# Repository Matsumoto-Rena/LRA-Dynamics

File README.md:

# LRA-Dynamics
-1201_LRA_web_v3
  - ArduinoIDEで開いて下さい 
  - WifiのSSIDとパスワードをパソコンの接続先と合わせます．
  - プログラムを実行するとシリアルモニタに数字が返ってくるのでブラウザにコピペしてください
  - rep12 res3で赤青方向 rep15 res1で緑黃方向に動きます

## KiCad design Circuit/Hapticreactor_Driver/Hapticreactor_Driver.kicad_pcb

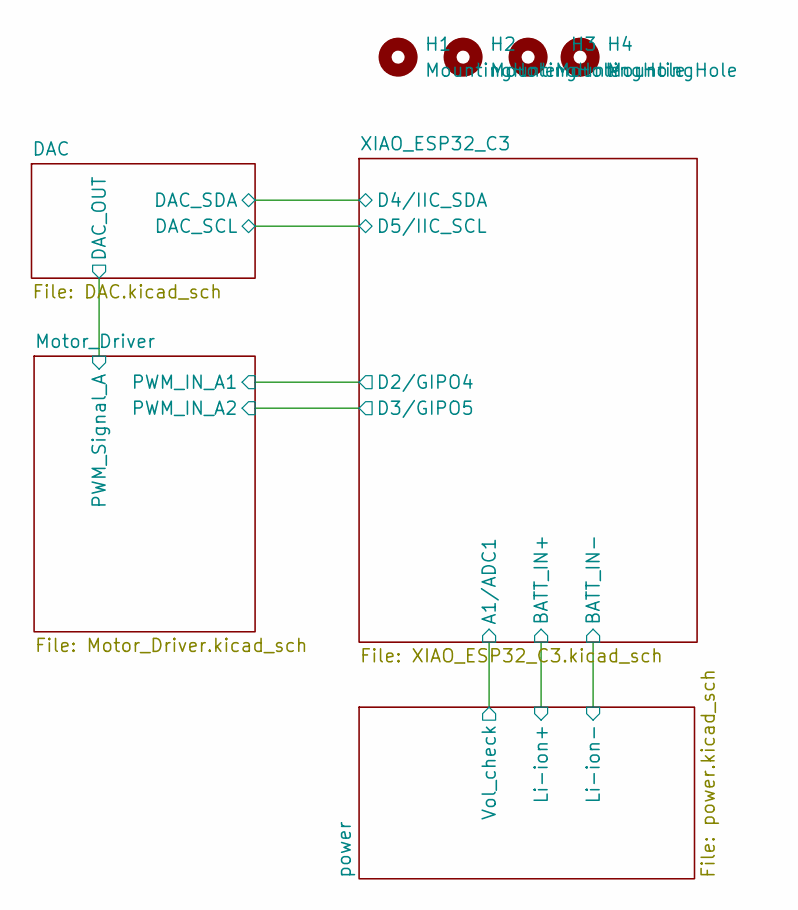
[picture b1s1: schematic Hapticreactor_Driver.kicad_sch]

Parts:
H1, H2, H3, H4: MountingHole; MountingHole_2.2mm_M2

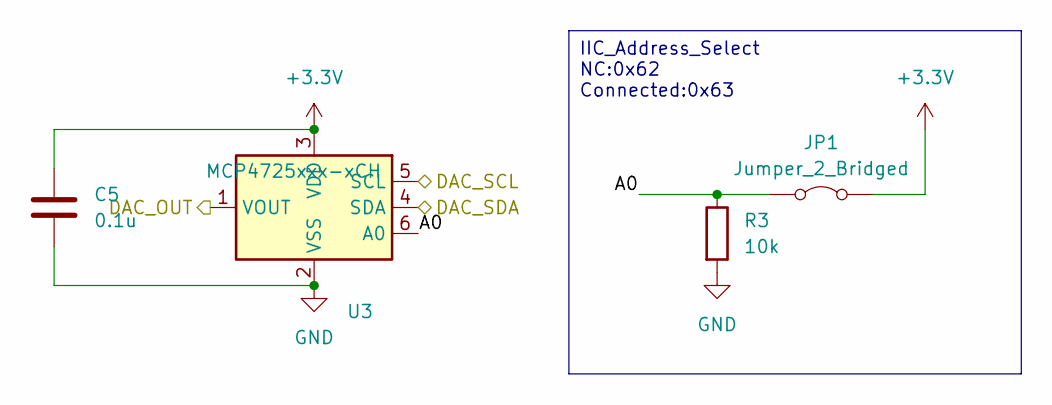
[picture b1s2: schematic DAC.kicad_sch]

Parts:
C5: 0.1u; C_0603_1608Metric_Pad1.08x0.95mm_HandSolder
JP1: Jumper_2_Bridged; SolderJumper-2_P1.3mm_Open_TrianglePad1.0x1.5mm
R3: 10k; R_0603_1608Metric_Pad0.98x0.95mm_HandSolder
U3: MCP4725xxx-xCH; SOT-23-6

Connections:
+3.3V: C5.1, JP1.2 (B), U3.3 (VDD); also elsewhere on the board
/DAC/A0: JP1.1 (A), R3.1, U3.6 (A0)
/DAC/DAC_OUT: U3.1 (VOUT); also elsewhere on the board
/DAC/DAC_SCL: U3.5 (SCL); also elsewhere on the board
/DAC/DAC_SDA: U3.4 (SDA); also elsewhere on the board
GND: C5.2, R3.2, U3.2 (VSS); also elsewhere on the board

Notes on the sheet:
IIC_Address_Select NC:0x62 Connected:0x63

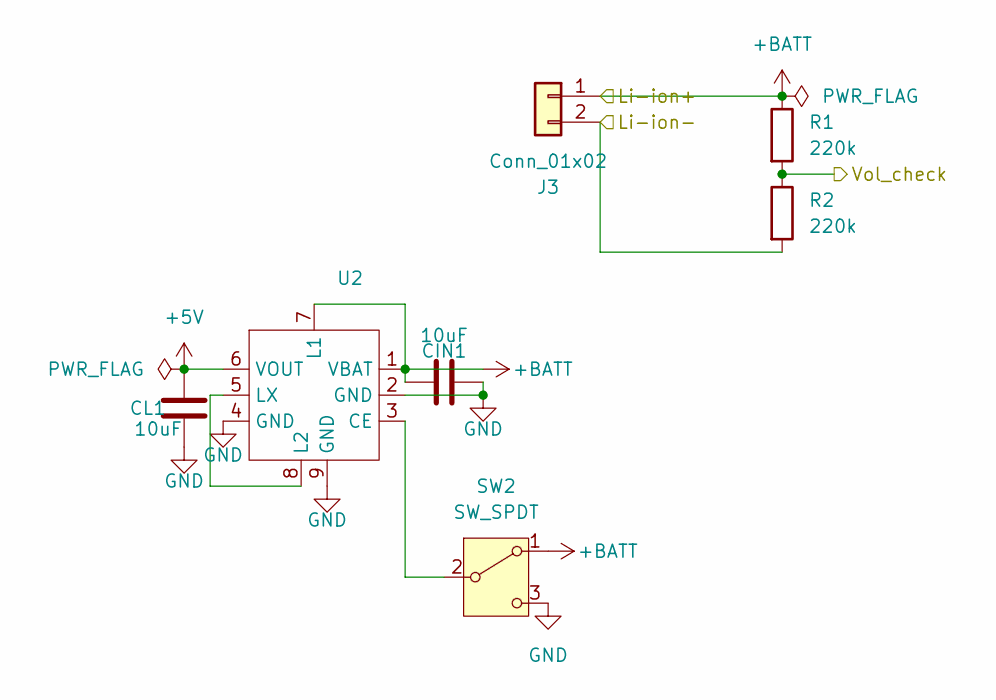
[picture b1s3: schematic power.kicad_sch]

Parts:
CIN1: 10uF; C_0603_1608Metric
CL1: 10uF; C_0603_1608Metric
J3: Conn_01x02; JST_PH_S2B-PH-K_1x02_P2.00mm_Horizontal
R1, R2: 220k; R_0603_1608Metric_Pad0.98x0.95mm_HandSolder
SW2: SW_SPDT; SSAJ120100
U2: XCL102D503CR-G

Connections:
+5V: CL1.2, U2.6 (VOUT); also elsewhere on the board
+BATT: CIN1.1, J3.1, R1.1, SW2.1 (A), U2.1 (VBAT), U2.7 (L1); also elsewhere on the board
/XIAO_ESP32_C3/A1/ADC1: R1.2, R2.1; also elsewhere on the board
/XIAO_ESP32_C3/BATT_IN-: J3.2, R2.2; also elsewhere on the board
GND: CIN1.2, CL1.1, SW2.3 (C), U2.2 (GND), U2.4 (GND), U2.9 (GND); also elsewhere on the board
unnamed: SW2.2 (B), U2.3 (CE)
unnamed: U2.5 (LX), U2.8 (L2)

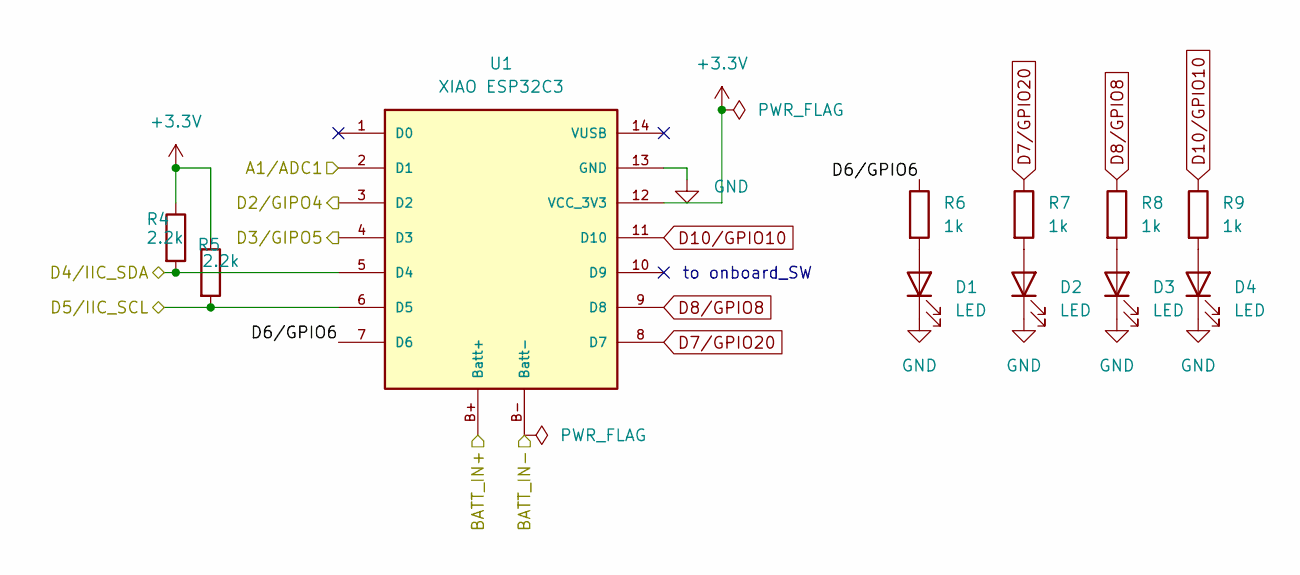
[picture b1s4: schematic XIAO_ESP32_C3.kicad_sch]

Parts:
D1, D2, D3, D4: LED; LED_0603_1608Metric
R4, R5: 2.2k; R_0603_1608Metric_Pad0.98x0.95mm_HandSolder
R6, R7, R8, R9: 1k; R_0603_1608Metric_Pad0.98x0.95mm_HandSolder
U1: XIAO ESP32C3; xiao_esp32c3

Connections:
+3.3V: R4.1, R5.1, U1.12 (VCC_3V3); also elsewhere on the board
+BATT: U1.B+ (Batt+); also elsewhere on the board
/DAC/DAC_SCL: R5.2, U1.6 (D5); also elsewhere on the board
/DAC/DAC_SDA: R4.2, U1.5 (D4); also elsewhere on the board
/Motor_Driver/PWM_IN_A1: U1.3 (D2); also elsewhere on the board
/Motor_Driver/PWM_IN_A2: U1.4 (D3); also elsewhere on the board
/XIAO_ESP32_C3/A1/ADC1: U1.2 (D1); also elsewhere on the board
/XIAO_ESP32_C3/BATT_IN-: U1.B- (Batt-); also elsewhere on the board
/XIAO_ESP32_C3/D6/GPIO6: R6.1, U1.7 (D6)
D7/GPIO20: R7.1, U1.8 (D7)
D8/GPIO8: R8.1, U1.9 (D8)
D10/GPIO10: R9.1, U1.11 (D10)
GND: D1.1 (K), D2.1 (K), D3.1 (K), D4.1 (K), U1.13 (GND); also elsewhere on the board
unnamed: D1.2 (A), R6.2
unnamed: D2.2 (A), R7.2
unnamed: D3.2 (A), R8.2
unnamed: D4.2 (A), R9.2

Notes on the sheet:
to onboard_SW

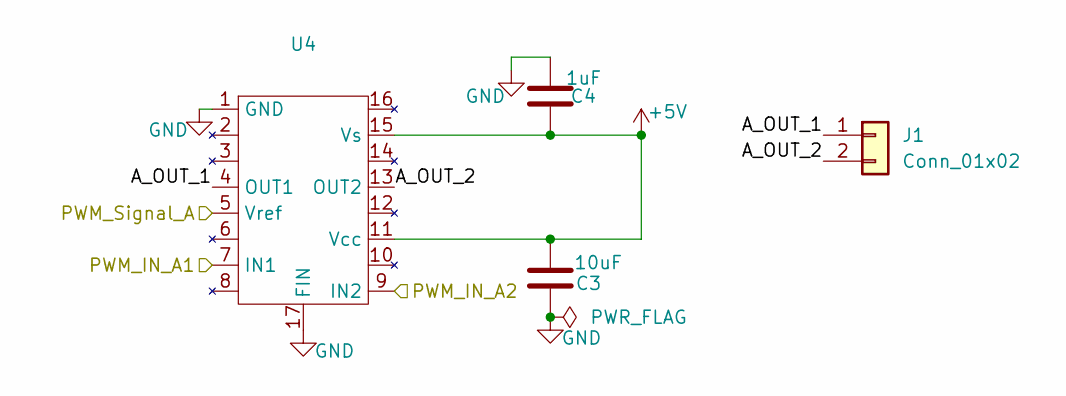
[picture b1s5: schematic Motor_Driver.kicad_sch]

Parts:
C3: 10uF; C_0603_1608Metric
C4: 1uF; C_0603_1608Metric
J1: Conn_01x02; PinHeader_1x02_P2.00mm_Vertical
U4: TA7291F

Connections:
+5V: C3.2, C4.1, U4.11 (Vcc), U4.15 (Vs); also elsewhere on the board
/DAC/DAC_OUT: U4.5 (Vref); also elsewhere on the board
/Motor_Driver/A_OUT_1: J1.1, U4.4 (OUT1)
/Motor_Driver/A_OUT_2: J1.2, U4.13 (OUT2)
/Motor_Driver/PWM_IN_A1: U4.7 (IN1); also elsewhere on the board
/Motor_Driver/PWM_IN_A2: U4.9 (IN2); also elsewhere on the board
GND: C3.1, C4.2, U4.1 (GND), U4.17 (FIN); also elsewhere on the board

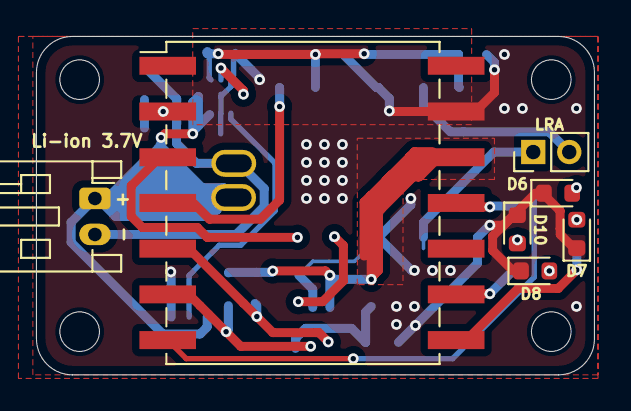
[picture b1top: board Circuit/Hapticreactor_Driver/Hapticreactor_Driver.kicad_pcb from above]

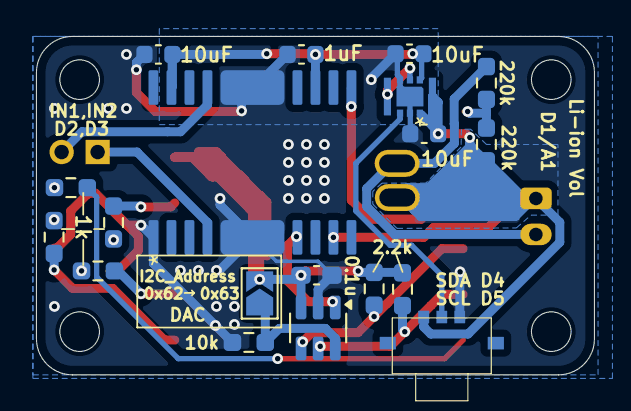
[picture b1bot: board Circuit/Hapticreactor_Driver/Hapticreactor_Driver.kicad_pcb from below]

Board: 2 copper layers, 31.0 x 18.8 mm, 30 parts (19 on the bottom side), 24 nets.

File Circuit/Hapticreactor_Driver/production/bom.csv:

Designator,Footprint,Quantity,Value,LCSC Part #
"C3, CIN1, CL1",0603,3,10uF,
C4,0603,1,1uF,
C5,0603,1,0.1u,
"D1, D2, D3, D4",0603,4,LED,
J1,PinHeader_1x02_P2.00mm_Vertical,1,Conn_01x02,
J3,JST_PH_S2B-PH-K_1x02_P2.00mm_Horizontal,1,Conn_01x02,
JP1,SolderJumper-2_P1.3mm_Open_TrianglePad1.0x1.5mm,1,Jumper_2_Bridged,
"R1, R2",0603,2,220k,
R3,0603,1,10k,
"R4, R5",0603,2,2.2k,
"R6, R7, R8, R9",0603,4,1k,
SW2,SSAJ120100,1,SW_SPDT,
U1,xiao_esp32c3,1,XIAO ESP32C3,
U2,XCL102D503CR-G,1,~,
U3,SOT-23-6,1,MCP4725xxx-xCH,
U4,TA7291F,1,~,

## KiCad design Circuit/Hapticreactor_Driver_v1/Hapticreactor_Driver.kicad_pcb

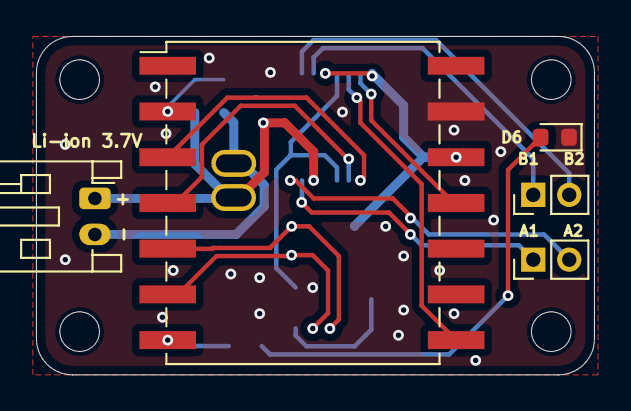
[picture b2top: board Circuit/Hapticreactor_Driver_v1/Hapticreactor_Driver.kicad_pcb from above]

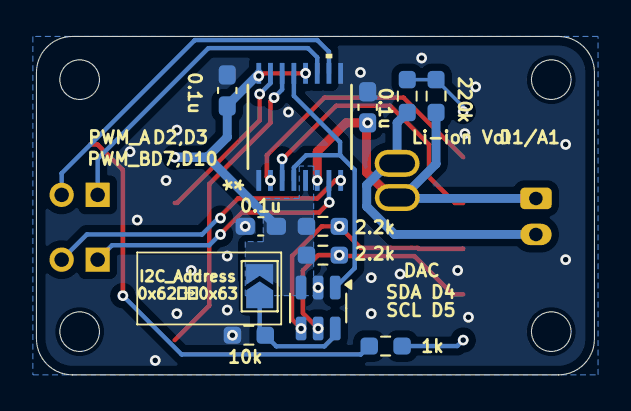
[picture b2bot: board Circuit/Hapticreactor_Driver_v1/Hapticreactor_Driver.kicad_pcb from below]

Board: 2 copper layers, 31.0 x 18.8 mm, 21 parts (12 on the bottom side), 19 nets.

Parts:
C1, C2, C5: 0.1u; C_0603_1608Metric_Pad1.08x0.95mm_HandSolder
D1: LED; LED_0603_1608Metric
H1, H2, H3, H4: MountingHole; MountingHole_2.2mm_M2
J1, J2: Conn_01x02; PinHeader_1x02_P2.00mm_Vertical
J3: Conn_01x02; JST_PH_S2B-PH-K_1x02_P2.00mm_Horizontal
JP1: Jumper_2_Bridged; SolderJumper-2_P1.3mm_Open_TrianglePad1.0x1.5mm
R1, R2: 220k; R_0603_1608Metric_Pad0.98x0.95mm_HandSolder
R3: 10k; R_0603_1608Metric_Pad0.98x0.95mm_HandSolder
R4, R5: 2.2k; R_0603_1608Metric_Pad0.98x0.95mm_HandSolder
R6: 1k; R_0603_1608Metric_Pad0.98x0.95mm_HandSolder
U1: XIAO ESP32C3; xiao_esp32c3
U2: TB6552FNG_C_8_EL; TB6552FNG
U3: MCP4725xxx-xCH; SOT-23-6

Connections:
+3.3V: C1.1, C5.1, JP1.2 (B), R4.1, R5.1, U1.12 (VCC_3V3), U2.5 (ASTBY), U2.12 (BSTBY), U2.16 (VCC), U3.3 (VDD)
+BATT: C2.1, J3.1, R1.1, U1.B+ (Batt+), U2.6 (VM)
/DAC/A0: JP1.1 (A), R3.1, U3.6 (A0)
/DAC/DAC_OUT: U2.4 (APWM), U2.13 (BPWM), U3.1 (VOUT)
/DAC/DAC_SCL: R5.2, U1.6 (D5), U3.5 (SCL)
/DAC/DAC_SDA: R4.2, U1.5 (D4), U3.4 (SDA)
/Motor_Driver/A_OUT_1: J1.1, U2.7 (AO1)
/Motor_Driver/A_OUT_2: J1.2, U2.8 (AO2)
/Motor_Driver/B_OUT_1: J2.1, U2.11 (BO1)
/Motor_Driver/B_OUT_2: J2.2, U2.10 (BO2)
/Motor_Driver/PWM_IN_A1: U1.3 (D2), U2.2 (AIN1)
/Motor_Driver/PWM_IN_A2: U1.4 (D3), U2.3 (AIN2)
/Motor_Driver/PWM_IN_B1: U1.11 (D10), U2.15 (BIN1)
/Motor_Driver/PWM_IN_B2: U1.8 (D7), U2.14 (BIN2)
/XIAO_ESP32_C3/A1/ADC1: R1.2, R2.1, U1.2 (D1)
/XIAO_ESP32_C3/BATT_IN-: J3.2, R2.2, U1.B- (Batt-)
/XIAO_ESP32_C3/D6/GPIO6: R6.1, U1.7 (D6)
GND: C1.2, C2.2, C5.2, D1.1 (K), R3.2, U1.13 (GND), U2.1 (GND), U2.9 (PGND), U3.2 (VSS)
unnamed: D1.2 (A), R6.2

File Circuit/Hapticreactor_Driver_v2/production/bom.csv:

Designator,Footprint,Quantity,Value,LCSC Part #
"C1, C2, C5",0603,3,0.1u,
D1,0603,1,LED,
"J1, J2",PinHeader_1x02_P2.00mm_Vertical,2,Conn_01x02,
J3,JST_PH_S2B-PH-K_1x02_P2.00mm_Horizontal,1,Conn_01x02,
JP1,SolderJumper-2_P1.3mm_Open_TrianglePad1.0x1.5mm,1,Jumper_2_Bridged,
"R1, R2",0603,2,220k,
R3,0603,1,10k,
"R4, R5",0603,2,2.2k,
R6,0603,1,1k,
U1,xiao_esp32c3,1,XIAO ESP32C3,
U2,TB6552FNG,1,TB6552FNG_C_8_EL,
U3,SOT-23-6,1,MCP4725xxx-xCH,

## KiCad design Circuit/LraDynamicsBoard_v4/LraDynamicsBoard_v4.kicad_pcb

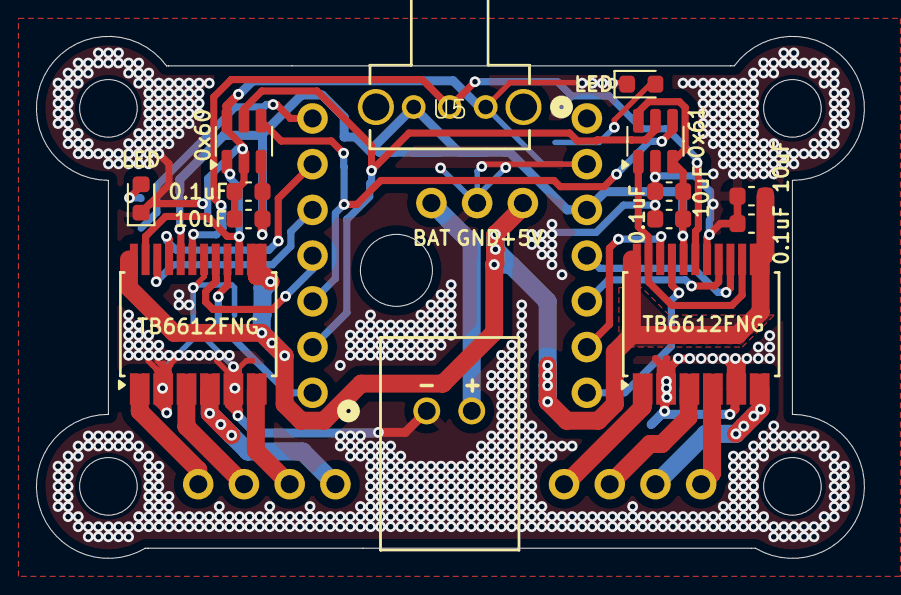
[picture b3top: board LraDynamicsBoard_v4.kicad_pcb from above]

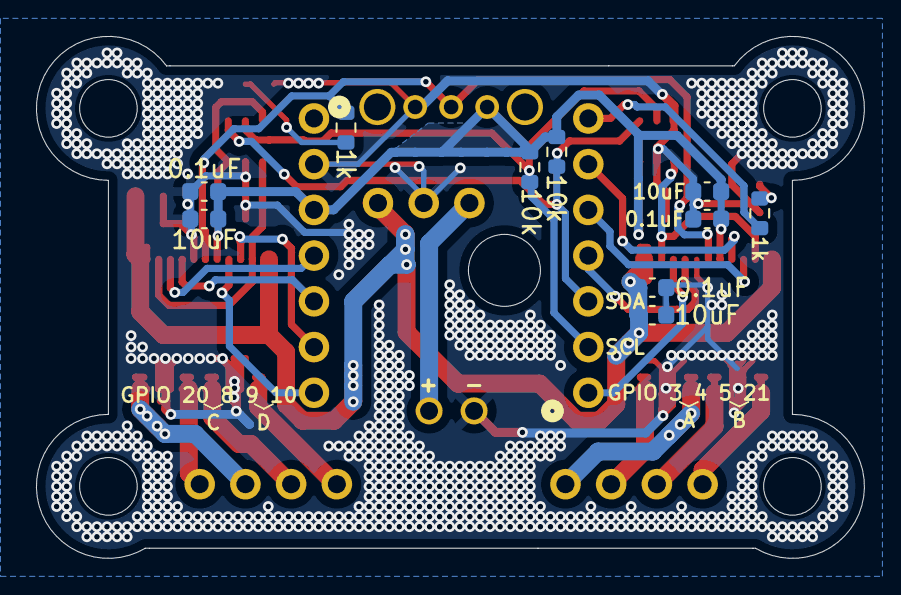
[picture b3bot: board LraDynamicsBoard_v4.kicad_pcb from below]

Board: 2 copper layers, 46.0 x 29.0 mm, 32 parts (10 on the bottom side), 28 nets.

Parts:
C1, C3, C6, C8, C10, C11: 0.1uF; C_0603_1608Metric
C2, C4, C12, C13, C14, C15: 10uF; C_0603_1608Metric
D1, D2: LED; LED_0603_1608Metric
H1, H2, H3, H4: MountingHole; MountingHole_3.2mm_M3
J1, J2: Conn_01x04; KF128-4P
J3: Conn_01x03; XCL103
J4: Conn_01x02; CONN_S2B-XH-A-1LFSN_JST
R1, R2: 10k; R_0603_1608Metric
R5, R6: 1k; R_0603_1608Metric
SW1: SW_SPDT; OS102011MA1QN1_CNK
U1, U2: MCP4725xxx-xCH; SOT-23-6
U3, U4: TB6612FNG; SSOP-24_5.3x8.2mm_P0.65mm
U5: XiaoEsp32C3

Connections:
+3V3: C1.1, C2.1, C3.1, C4.1, C6.1, C10.1, C13.1, C15.1, R1.1, R2.1, SW1.3 (C), U1.3 (VDD), U2.3 (VDD), U2.6 (A0), U3.20 (VCC), U4.20 (VCC), U5.11 (3V3)
+5V: C8.1, C11.1, C12.1, C14.1, J3.3, U3.13 (VM2), U3.14 (VM3), U3.24 (VM1), U4.13 (VM2), U4.14 (VM3), U4.24 (VM1)
ANALOG_1: U1.1 (VOUT), U3.15 (PWMB), U3.23 (PWMA)
ANALOG_2: U2.1 (VOUT), U4.15 (PWMB), U4.23 (PWMA)
BAT: J3.1, J4.2
D_A1: U3.21 (AIN1), U5.1 (D1)
D_A2: U3.22 (AIN2), U5.2 (D2)
D_B1: U3.17 (BIN1), U5.3 (D3)
D_B2: U3.16 (BIN2), U5.6 (D6)
D_C1: U4.21 (AIN1), U5.7 (D7)
D_C2: U4.22 (AIN2), U5.8 (D8)
D_D1: U4.17 (BIN1), U5.9 (D9)
D_D2: U4.16 (BIN2), U5.10 (D10)
GND: C1.2, C2.2, C3.2, C4.2, C6.2, C8.2, C10.2, C11.2, C12.2, C13.2, C14.2, C15.2, D1.1 (K), D2.1 (K), J3.2, J4.1, SW1.1 (A), U1.2 (VSS), U1.6 (A0), U2.2 (VSS), U3.3 (PGND1), U3.4 (PGND1), U3.9 (PGND2), U3.10 (PGND2), U3.18 (GND), U4.3 (PGND1), U4.4 (PGND1), U4.9 (PGND2), U4.10 (PGND2), U4.18 (GND), U5.12 (GND)
unnamed: D1.2 (A), R5.2
unnamed: D2.2 (A), R6.2
unnamed: R6.1, U5.0 (D0)
OUT_A1: J1.1, U3.1 (AO1), U3.2 (AO1)
OUT_A2: J1.2, U3.5 (AO2), U3.6 (AO2)
OUT_B1: J1.3, U3.11 (BO1), U3.12 (BO1)
OUT_B2: J1.4, U3.7 (BO2), U3.8 (BO2)
OUT_C1: J2.1, U4.1 (AO1), U4.2 (AO1)
OUT_C2: J2.2, U4.5 (AO2), U4.6 (AO2)
OUT_D1: J2.3, U4.11 (BO1), U4.12 (BO1)
OUT_D2: J2.4, U4.7 (BO2), U4.8 (BO2)
SCL: R1.2, U1.5 (SCL), U2.5 (SCL), U5.5 (D5)
SDA: R2.2, U1.4 (SDA), U2.4 (SDA), U5.4 (D4)
STBY: R5.1, SW1.2 (B), U3.19 (STBY), U4.19 (STBY)

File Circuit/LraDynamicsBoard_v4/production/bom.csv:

Designator,Footprint,Quantity,Value,LCSC Part #
"C1, C10, C11, C3, C6, C8",0603,6,0.1uF,
"C12, C13, C14, C15, C2, C4",0603,6,10uF,
D1,0603,1,ACT,
D2,0603,1,IO2,
"J1, J2",KF128-4P,2,Conn_01x04,
J3,XCL103,1,Conn_01x03,
J4,CONN_S2B-XH-A-1LFSN_JST,1,Conn_01x02,
"R1, R2",0603,2,10k,
"R5, R6",0603,2,1k,
SW1,OS102011MA1QN1_CNK,1,SW_SPDT,
"U1, U2",SOT-23-6,2,MCP4725xxx-xCH,
"U3, U4",SSOP-24_5.3x8.2mm_P0.65mm,2,TB6612FNG,
U5,XiaoEsp32C6,1,~,

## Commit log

2025-08-30 add sample programs
2025-09-01 1秒毎に電流を流す方向が変化する.非対称振動による移動ができてそうな感じがする
2025-09-07 非対称なSin波らしきものを出すことに成功
2025-09-07 アナログ波形をMDに入力しようと試みた
2025-09-12 実験装置のCAD,Arduinoコードをアップロード
2025-09-20 M5StackBasicのDACを使って非対称振動,対象振動を発生させることに成功
2025-09-21 試行錯誤の末,マイクロSDカード内のwavファイルをループ再生することに成功.
2025-09-22 0922ファイルを追加.見事な非対称波形を出してくれます.また,LRAの移動もできているような気がする
2025-09-22 コード先頭に説明文を追加
2025-09-22 手で持つといい感じに二自由度で力を感じる.しかし,床において動かすと,床に接触していない方のLRAの振動がうまく伝わらず思った方向には動かない固定台の構造を変えるべきかもしれない
2025-09-25 LRA2つとM5Stickを一体にし,DS4からの無線コントールすることで,完全独立に動かすことができた,ケーブルうんぬんに悩まなくてすむ.しかし重いのか,移動はしない
2025-09-29 https://robohanactive.slack.com/archives/C08RF0U7A49/p1759132342633789
2025-09-30 まだ途中だけどLRAを無線で動かせてリチウムイオン電池載せれて,MD4チャンネルある基板作ってます.回路図は結構できてきた
2025-10-18 最初に発注した基板を追加
2025-10-18 ハプティックリアクタ用基板回路図アップロード
2025-10-19 ハプティックリアクタ用基板完成
2025-10-20 発注した基板でDACを動かすコードArduinoIDE使用
2025-10-20 頑張って350Hzくらいの正弦波の出力に成功
2025-10-21 VMをバッテリ入力に変更，バッテリ周りの間違いを訂正
2025-11-07 ハプティックリアクタ用基板のCadをアップロード
2025-11-07 YODAI基板で動いた
2025-11-07 さっきはうまくコミットできていませんでした，これは陽大ボードで動いたプログラムです
2025-11-11 index.htmlを追加
2025-11-11 Bluetooth接続に成功
2025-11-12 秋野基板で動かそうとした．DACからの出力はうまくいったもののMDが動かない
2025-11-12 再アップロード
2025-11-15 MDをTB6612FNG
2025-11-15 MDTB6612FNGに変更
2025-11-16 秋野の回路に昇圧DCDCつけて東芝MDつけた
2025-11-17 新しい基板つくった
2025-11-17 ベタとかをちゃんとした．もう発注しても良さそう
2025-11-17 スイッチを追加した．とりあえずこれで一旦発注しました
2025-11-22 赤点を認識して座標を出すプログラム
2025-11-22 カメラの起動部分を修正
2025-11-22 カメラの表示部分を修正
2025-11-22 scriptを修正
2025-11-22 videoの部分を基に戻す
2025-11-22 認識の閾値を下げる
2025-11-22 認識の閾値をさらに下げる
2025-11-22 BindingErrorの修正
2025-11-22 閾値を厳格にする
2025-11-22 閾値をさらに厳格にする
2025-11-22 丸を認識するよう修正
2025-11-22 赤の認識閾値をさらに厳格にする
2025-11-22 赤丸はノイズが多いので，青丸を認識することにする
2025-11-22 画面の端の方の認識制度を上げるように改良
2025-11-22 座標をWebに表示
2025-11-30 ハプティックリアクタをウェブから動かすコードを追加
2025-11-30 Pattern1でres12 rep3 Pattern2でres15 rep1にするとかなりいい感じに動きます
2025-12-11 画像の表示範囲を変更
2025-12-11 画像の表示範囲を変更．反映されなかったのでもう一度
2025-12-11 画像の比率を1：1に
2025-12-11 真っ白になるのを修正
2025-12-11 エラー修正
2025-12-11 表示画面を大きく修正
2025-12-11 視野を広げる
2025-12-11 縦を広くする
2025-12-11 モード追加
2025-12-11 モードによってヘッダを追加
2025-12-11 モード1：座標をとる．モード2：フィードバック用
2025-12-12 コメント修正
2025-12-12 振動はしないが方向指示はできている
2025-12-12 パラメタ調整
2025-12-12 右と左の指令を逆にする．Bleデータ送信頻度を下げる
2025-12-12 データ出力までできるようにした
2025-12-13 赤点を認識するように変更
2025-12-13 解析用プログラム追加．Webも原点認識の部分を変更
2025-12-13 緑店認識に変更
2025-12-13 青点認識に戻す
2025-12-13 方向指示の番号を修正
2025-12-13 方向指示の番号を修正,
2025-12-14 モード2にフィードバック追加
2025-12-14 今日のはじめの状態に戻す
2025-12-14 3秒後に停止をなくす
2025-12-14 3秒後に停止
2025-12-14 右と左のコマンド追加
2025-12-15 実験データ追加．向きを判定できるようにする
2025-12-15 初めに向いている向きをy軸正とする
2025-12-16 方向も図に表示，約4秒間データをとる使用に変更
2025-12-16 送信頻度を下げる
2025-12-16 大きい青丸と小さい青丸で前後を判別
2025-12-17 送信タイミングを早める
2025-12-18 色々変えてる
2025-12-18 とりまコミット
2026-02-21 黄→赤をビビぞうの向きとして認識します．move1~move4まで4種類の動作モードがあります．move1,2の19 3では前後，move4の5 30では左右に動きます
2026-02-21 ビビぞう基本の3パーツをアップロード
2026-02-21 関係無いファイルは削除
2026-02-23 videoまわりの修正
2026-02-23 script URL変更
2026-02-23 カメラまわりを前と同じ仕様に変更
2026-02-23 cv = window.cv;が抜けてた
2026-02-23 実行順序の変更
2026-02-23 前の方式に改編
2026-02-23 webassemblyの変更？
2026-02-23 open cv をローカル環境に入れる
2026-02-23 open cv を入れる
2026-02-23 opencv を追加
2026-02-23 scriptのところ変更
2026-02-23 通信まわりを変更
2026-02-23 通信まわりを変更したが，scriptも書き換えられたので，ローカルに戻す
2026-02-26 パラメタをデフォルトにする
2026-02-26 黄色と赤丸を読むようにする
2026-02-26 htmlをhtml css jsファイルに分割
2026-02-26 fix: cssの変更内容を反映
2026-02-26 座標をブラウザで計算する方式に変更
2026-02-26 座標指定可能にする
2026-02-26 方向が逆だったので，逆にする
2026-02-26 追従アルゴリズムを変更
2026-02-26 前後の運動を優先
2026-02-26 アルゴリズム変更
2026-02-26 値が変化した時だけ送信
2026-02-26 fix タイプミスの修正，これでAngle取れるかな
2026-02-26 analysis追加，ウェブのバグを改善
